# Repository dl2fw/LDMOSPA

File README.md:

# LDMOSPA
LDMOS PA based on the design of DJ0ABR - case from PCB Material<br>
Output power 750 or 1500 Watt - depends on if you use 1 or 2 double mosfets<br>
The PA can be either water or air cooled - the case makes both possible - I prefer the water cooled version<br>
The front has the same size as DB5AT's Wolf SDR case based on PCB Material<br>
All gerbers are available here<br>
I tried to gather all schematics and gerbers for the PA<br>
Also BOMS for Digikey, Reichelt and Aliexpress are in the BOM folder<br>
The water cooler is a ready available one (Digikey,...) for app. 65€<br>

Link to dj0abr's homepage with further information in german and english:

https://www.dj0abr.de/

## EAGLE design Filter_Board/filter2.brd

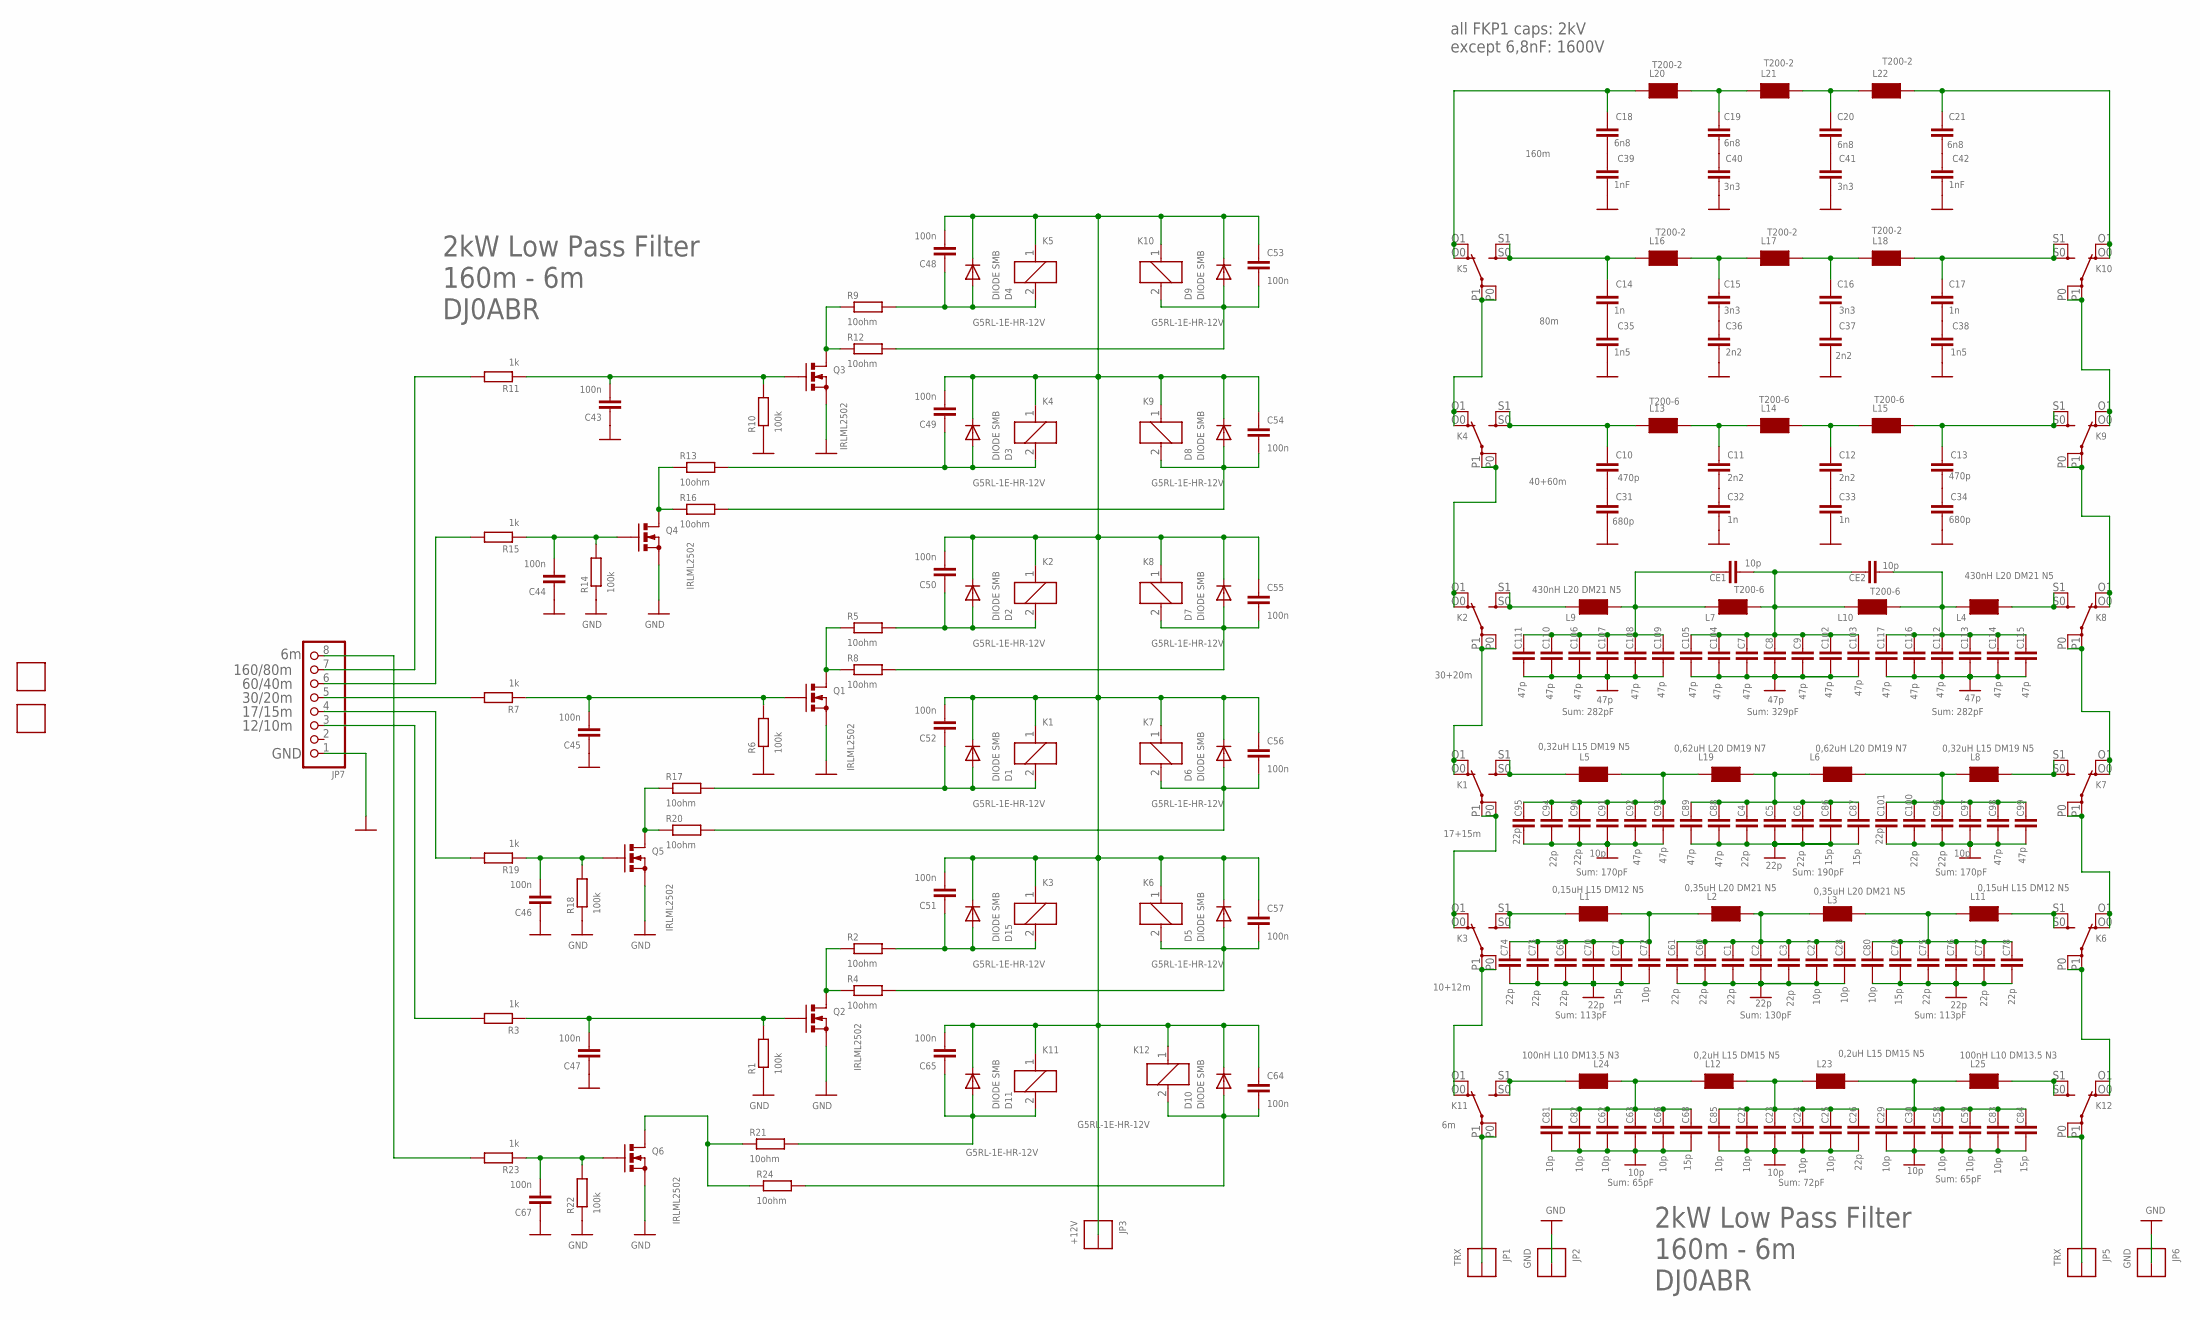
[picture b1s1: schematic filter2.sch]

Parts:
C1, C2, C3, C4, C5, C6, C26, C60, C61, C69, C70, C73, C74, C75, C76, C77, C78, C90, C94, C95, C96, C100, C101: 22p; C1812K
C7, C8, C9, C88, C89, C92, C93, C98, C99, C102, C103, C104, C105, C106, C107, C108, C109, C110, C111, C112, C113, C114, C115, C116, C117: 47p; C1812K
C10, C13: 470p; C150-064X183
C11, C12, C36, C37: 2n2; C225-074X268
C14, C17, C32, C33: 1n; C225-062X268
C15, C16: 3n3; C225-074X268
C18, C19, C20, C21: 6n8; C225-074X268
C22, C23, C24, C25, C27, C28, C29, C30, C58, C59, C62, C63, C66, C72, C80, C81, C82, C83, C85, C91, C97: 10p; C1812K
C31, C34: 680p; C150-064X183
C35, C38: 1n5; C225-074X268
C39, C42: 1nF; C225-074X268
C40, C41: 3n3; C225-087X268
C43, C44, C45, C46, C47, C48, C49, C50, C51, C52, C53, C54, C55, C56, C57, C64, C65, C67: 100n; C0603K
C68, C71, C79, C84, C86, C87: 15p; C1812K
CE1, CE2: 10p; C1812K
D1, D2, D3, D4, D5, D6, D7, D8, D9, D10, D11, D15: DIODE SMB; SMB
FID1, FID2: FIDUCIAL
JP1, JP5: TRX; THICKPIN
JP2, JP6: GND; THICKPIN
JP3: +12V; THICKPIN
JP7: PINHD-1X8; 1X08
K1, K2, K3, K4, K5, K6, K7, K8, K9, K10, K11, K12: G5RL-1E-HR-12V; G2RE
L1, L11: 0,15uH L15 DM12 N5; LUFTSPULE_L15XDM14
L2, L3: 0,35uH L20 DM21 N5; LUFTSPULE_L17XDM20
L4, L9: 430nH L20 DM21 N5; LUFTSPULE_20X20RM20
L5, L8: 0,32uH L15 DM19 N5; LUFTSPULR_L15XDM20
L6, L19: 0,62uH L20 DM19 N7; LUFTSPULE_20X20RM20
L7, L10, L13, L14, L15: T200-6; KERN200_STEHEND_2PIN
L12, L23: 0,2uH L15 DM15 N5; LUFTSPULE_L15XDM14
L16, L17, L18, L20, L21, L22: T200-2; KERN200_STEHEND_2PIN
L24, L25: 100nH L10 DM13.5 N3; LUFTSPULE_10X13K5
Q1, Q2, Q3, Q4, Q5, Q6: IRLML2502; SOT23
R1, R6, R10, R14, R18, R22: 100k; R0603
R2, R4, R5, R8, R9, R12, R13, R16, R17, R20, R21, R24: 10ohm; R0603
R3, R7, R11, R15, R19, R23: 1k; R0603

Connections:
+12V: C48.2, C49.2, C50.2, C51.2, C52.2, C53.1, C54.1, C55.1, C56.1, C57.1, C64.1, C65.2, D1.C, D2.C, D3.C, D4.C, D5.C, D6.C, D7.C, D8.C, D9.C, D10.C, D11.C, D15.C, JP3.1, K1.1, K2.1, K3.1, K4.1, K5.1, K6.1, K7.1, K8.1, K9.1, K10.1, K11.1, K12.1
GND: C1.2, C2.2, C3.2, C4.2, C5.2, C6.2, C7.2, C8.2, C9.2, C22.2, C23.2, C24.2, C25.2, C26.2, C27.2, C28.2, C29.2, C30.2, C31.2, C32.2, C33.2, C34.2, C35.2, C36.2, C37.2, C38.2, C39.2, C40.2, C41.2, C42.2, C43.1, C44.1, C45.1, C46.1, C47.1, C58.2, C59.2, C60.2, C61.2, C62.2, C63.2, C66.2, C67.1, C68.2, C69.2, C70.2, C71.2, C72.2, C73.2, C74.2, C75.2, C76.2, C77.2, C78.2, C79.2, C80.2, C81.2, C82.2, C83.2, C84.2, C85.2, C86.2, C87.2, C88.2, C89.2, C90.2, C91.2, C92.2, C93.2, C94.2, C95.2, C96.2, C97.2, C98.2, C99.2, C100.2, C101.2, C102.2, C103.2, C104.2, C105.2, C106.2, C107.2, C108.2, C109.2, C110.2, C111.2, C112.2, C113.2, C114.2, C115.2, C116.2, C117.2, JP2.1, JP6.1, JP7.1, Q1.2 (S), Q2.2 (S), Q3.2 (S), Q4.2 (S), Q5.2 (S), Q6.2 (S), R1.1, R6.1, R10.1, R14.1, R18.1, R22.1
unnamed: K6.P0, K6.P1, K12.O0 (O), K12.O1 (O)
unnamed: K3.S0 (S), K3.S1 (S), L1.P$1 (1)
unnamed: K1.P0, K1.P1, K3.O0 (O), K3.O1 (O)
unnamed: C75.1, C76.1, C77.1, C78.1, C79.1, C80.1, L3.P$2 (2), L11.P$1 (1)
unnamed: K1.S0 (S), K1.S1 (S), L5.P$1 (1)
unnamed: K1.O0 (O), K1.O1 (O), K2.P0, K2.P1
unnamed: C1.1, C2.1, C3.1, C27.1, C28.1, C60.1, C61.1, L2.P$2 (2), L3.P$1 (1)
unnamed: K2.S0 (S), K2.S1 (S), L9.P$1 (1)
unnamed: K2.O0 (O), K2.O1 (O), K4.P0, K4.P1
unnamed: K8.S0 (S), K8.S1 (S), L4.P$2 (2)
unnamed: K4.O0 (O), K4.O1 (O), K5.P0, K5.P1
unnamed: C106.1, C107.1, C108.1, C109.1, C110.1, C111.1, CE1.1, L7.1, L9.P$2 (2)
unnamed: K7.S0 (S), K7.S1 (S), L8.P$2 (2)
unnamed: Q2.3 (D), R2.1, R4.1
unnamed: K6.S0 (S), K6.S1 (S), L11.P$2 (2)
unnamed: K6.O0 (O), K6.O1 (O), K7.P0, K7.P1
unnamed: K7.O0 (O), K7.O1 (O), K8.P0, K8.P1
unnamed: K8.O0 (O), K8.O1 (O), K9.P0, K9.P1
unnamed: K9.O0 (O), K9.O1 (O), K10.P0, K10.P1
unnamed: C47.2, Q2.1 (G), R1.2, R3.1
unnamed: C90.1, C91.1, C92.1, C93.1, C94.1, C95.1, L5.P$2 (2), L19.P$1 (1)
unnamed: C4.1, C5.1, C6.1, C86.1, C87.1, C88.1, C89.1, L6.P$1 (1), L19.P$2 (2)
unnamed: C96.1, C97.1, C98.1, C99.1, C100.1, C101.1, L6.P$2 (2), L8.P$1 (1)
unnamed: C18.1, K5.O0 (O), K5.O1 (O), L20.1
unnamed: C7.1, C8.1, C9.1, C102.1, C103.1, C104.1, C105.1, CE1.2, CE2.1, L7.2, L10.1
unnamed: C112.1, C113.1, C114.1, C115.1, C116.1, C117.1, CE2.2, L4.P$1 (1), L10.2
unnamed: C10.1, K4.S0 (S), K4.S1 (S), L13.1
unnamed: C11.1, L13.2, L14.1
unnamed: C12.1, L14.2, L15.1
unnamed: C13.1, K9.S0 (S), K9.S1 (S), L15.2
unnamed: C14.1, K5.S0 (S), K5.S1 (S), L16.1
unnamed: C15.1, L16.2, L17.1
unnamed: C16.1, L17.2, L18.1
unnamed: C17.1, K10.S0 (S), K10.S1 (S), L18.2
unnamed: K3.P0, K3.P1, K11.O0 (O), K11.O1 (O)
unnamed: C19.1, L20.2, L21.1
unnamed: C20.1, L21.2, L22.1
unnamed: Q1.3 (D), R5.1, R8.1
unnamed: C45.2, Q1.1 (G), R6.2, R7.1
unnamed: Q3.3 (D), R9.1, R12.1
unnamed: C43.2, Q3.1 (G), R10.2, R11.1
unnamed: Q4.3 (D), R13.1, R16.1
unnamed: C44.2, Q4.1 (G), R14.2, R15.1
unnamed: Q5.3 (D), R17.1, R20.1
unnamed: C46.2, Q5.1 (G), R18.2, R19.1
unnamed: JP7.5, R7.2
unnamed: JP7.6, R15.2
unnamed: JP7.7, R11.2
unnamed: C22.1, C23.1, C24.1, C25.1, C26.1, C85.1, L12.P$2 (2), L23.P$1 (1)
unnamed: C21.1, K10.O0 (O), K10.O1 (O), L22.2
unnamed: C69.1, C70.1, C71.1, C72.1, C73.1, C74.1, L1.P$2 (2), L2.P$1 (1)
unnamed: C13.2, C34.1
unnamed: C21.2, C42.1
unnamed: C20.2, C41.1
unnamed: C19.2, C40.1
unnamed: C18.2, C39.1
unnamed: C10.2, C31.1
unnamed: C11.2, C32.1
unnamed: C12.2, C33.1
unnamed: C17.2, C38.1
unnamed: C16.2, C37.1
unnamed: C15.2, C36.1
unnamed: C14.2, C35.1
unnamed: JP7.4, R19.2
unnamed: JP7.3, R3.2
unnamed: JP1.1, K11.P0, K11.P1
unnamed: K11.S0 (S), K11.S1 (S), L24.P$1 (1)
unnamed: Q6.3 (D), R21.1, R24.1
unnamed: C62.1, C63.1, C66.1, C68.1, C81.1, C82.1, L12.P$1 (1), L24.P$2 (2)
unnamed: C29.1, C30.1, C58.1, C59.1, C83.1, C84.1, L23.P$2 (2), L25.P$1 (1)
unnamed: K12.S0 (S), K12.S1 (S), L25.P$2 (2)
unnamed: JP5.1, K12.P0, K12.P1
unnamed: C67.2, Q6.1 (G), R22.2, R23.1
unnamed: JP7.8, R23.2
R1: C50.1, D2.A, K2.2, R5.2
R2: C51.1, D15.A, K3.2, R2.2
R3: C52.1, D1.A, K1.2, R17.2
R4: C65.1, D11.A, K11.2, R21.2
R5: C49.1, D3.A, K4.2, R13.2
R8: C48.1, D4.A, K5.2, R9.2
RB6: C64.2, D10.A, K12.2, R24.2
RB10: C57.2, D5.A, K6.2, R4.2
RB15: C56.2, D6.A, K7.2, R20.2
RB20: C55.2, D7.A, K8.2, R8.2
RB40: C54.2, D8.A, K9.2, R16.2
RB80: C53.2, D9.A, K10.2, R12.2

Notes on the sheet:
10+12m
30+20m
40+60m
80m
160m
17+15m
160/80m
60/40m
30/20m
17/15m
12/10m
GND
2kW Low Pass Filter 160m - 6m DJ0ABR
all FKP1 caps: 2kV except 6,8nF: 1600V
Sum: 282pF
Sum: 329pF
Sum: 170pF
Sum: 190pF
Sum: 113pF
Sum: 130pF
Sum: 65pF
Sum: 72pF

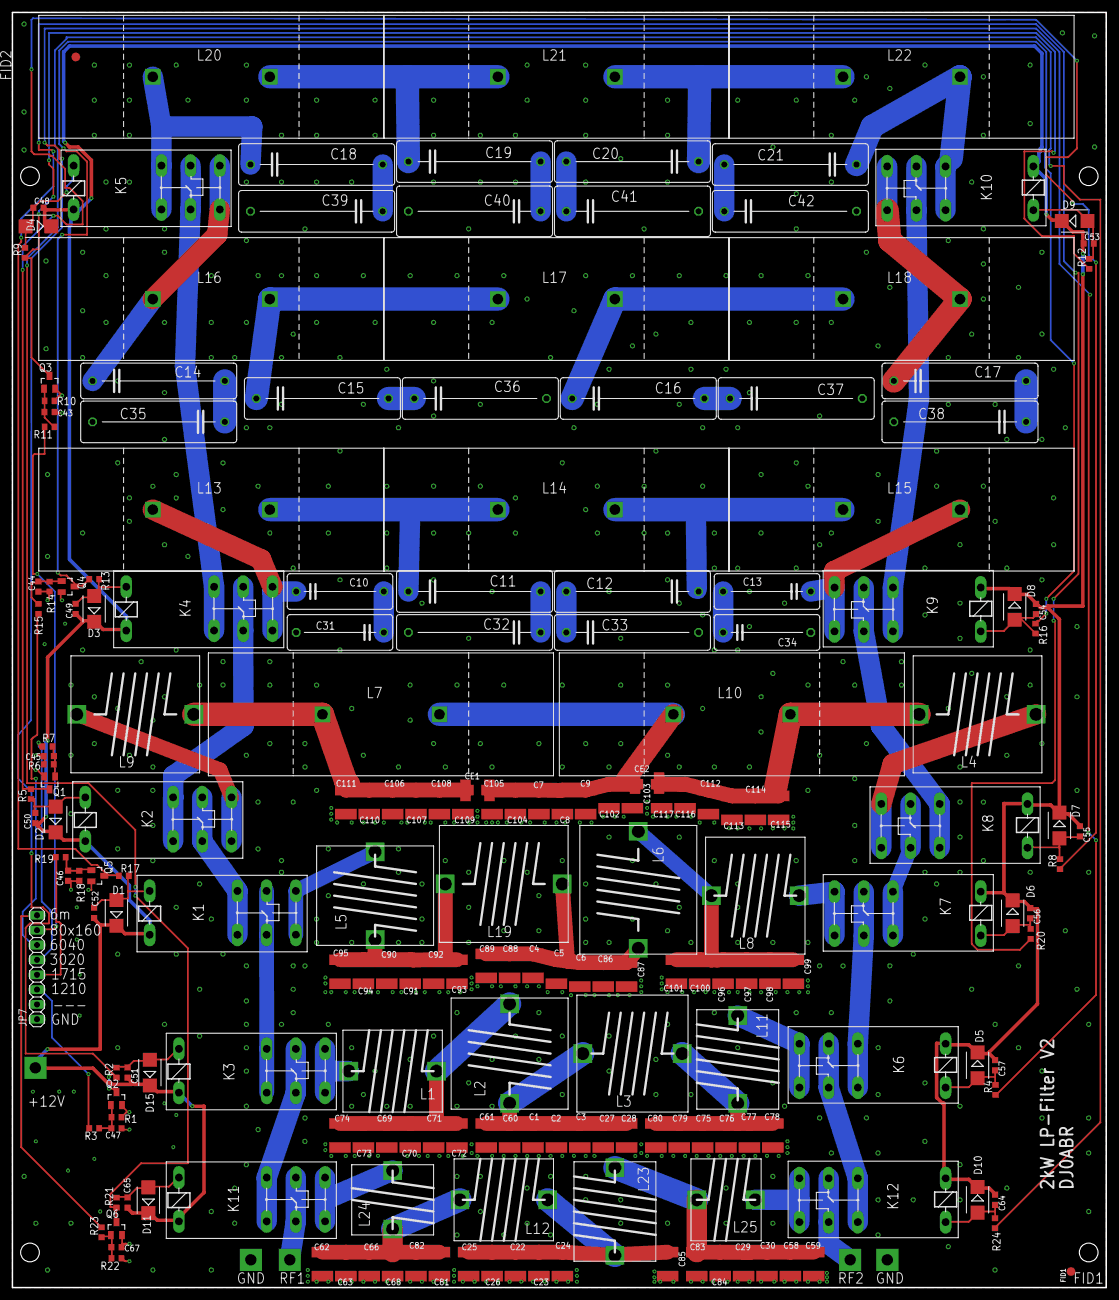
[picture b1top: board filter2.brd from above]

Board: 2 copper layers, 187.0 x 218.0 mm, 206 parts (0 on the bottom side), 88 nets.

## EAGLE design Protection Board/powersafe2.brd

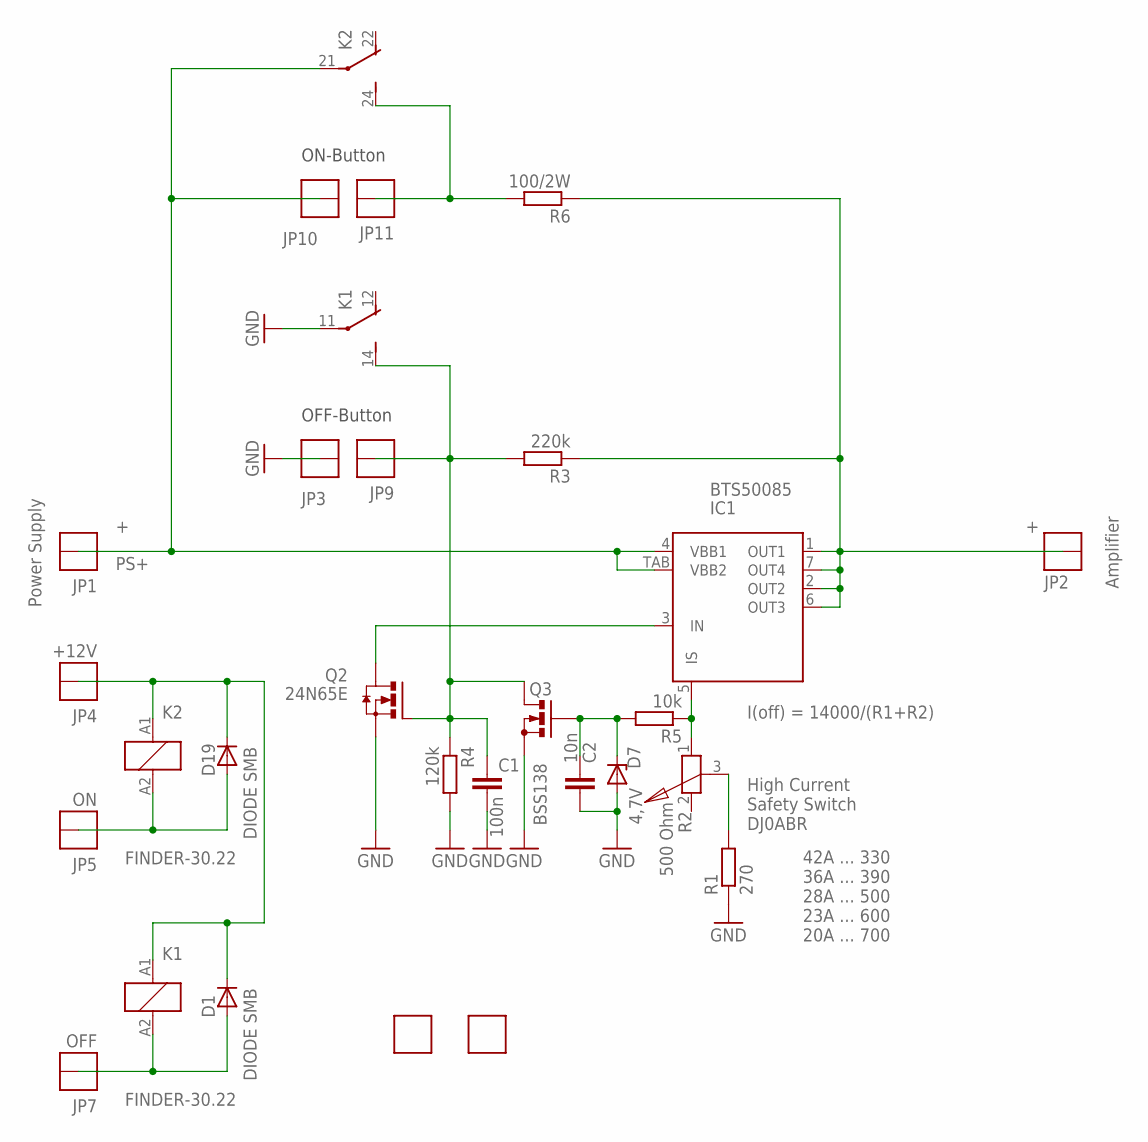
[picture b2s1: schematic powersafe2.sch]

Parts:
C1: 100n; C0603K
C2: 10n; C0603K
D1, D19: DIODE SMB; SMB
D7: 4,7V; SMA
FID1, FID2: FIDUCIAL
IC1: BTS50085; PG-TO220-7-4
JP1, JP2: THICKPINPIN_4QMM; PIN_4QMM
JP3, JP9, JP10, JP11: THICKPINSQUARE; THICKPIN
JP4: +12V; THICKPIN_OCT
JP5: ON; THICKPIN_OCT
JP7: OFF; THICKPIN_OCT
K1, K2: FINDER-30.22
Q2: 24N65E; D2PACK
Q3: BSS138; SOT23
R1: 270; R0603
R2: 500 Ohm; MINIPOTI
R3: 220k; R0603
R4: 120k; R0603
R5: 10k; R0603
R6: 100/2W; P0613/15

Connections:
GND: C1.2, C2.2, D7.A, JP3.1, K1.11, Q2.3 (S), Q3.2 (S), R1.1, R4.2
unnamed: C2.1, D7.C, Q3.1 (G), R5.2
unnamed: IC1.3 (IN), Q2.2 (D)
unnamed: C1.1, JP9.1, K1.14 (S), Q2.1 (G), Q3.3 (D), R3.2, R4.1
unnamed: IC1.5 (IS), R2.1, R5.1
unnamed: JP11.1, K2.24 (S), R6.2
unnamed: D19.A, JP5.1, K2.A2 (2)
unnamed: D1.C, D19.C, JP4.1, K1.A1 (1), K2.A1 (1)
unnamed: R1.2, R2.3
unnamed: D1.A, JP7.1, K1.A2 (2)
PA+: IC1.1 (OUT1), IC1.2 (OUT2), IC1.6 (OUT3), IC1.7 (OUT4), JP2.P$1, R3.1, R6.1
PS+: IC1.4 (VBB1), IC1.TAB (VBB2), JP1.P$1, JP10.1, K2.21

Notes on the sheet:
I(off) = 14000/(R1+R2)
High Current Safety Switch DJ0ABR
42A ... 330 36A ... 390 28A ... 500 23A ... 600 20A ... 700
OFF-Button
ON-Button
Amplifier
Power Supply

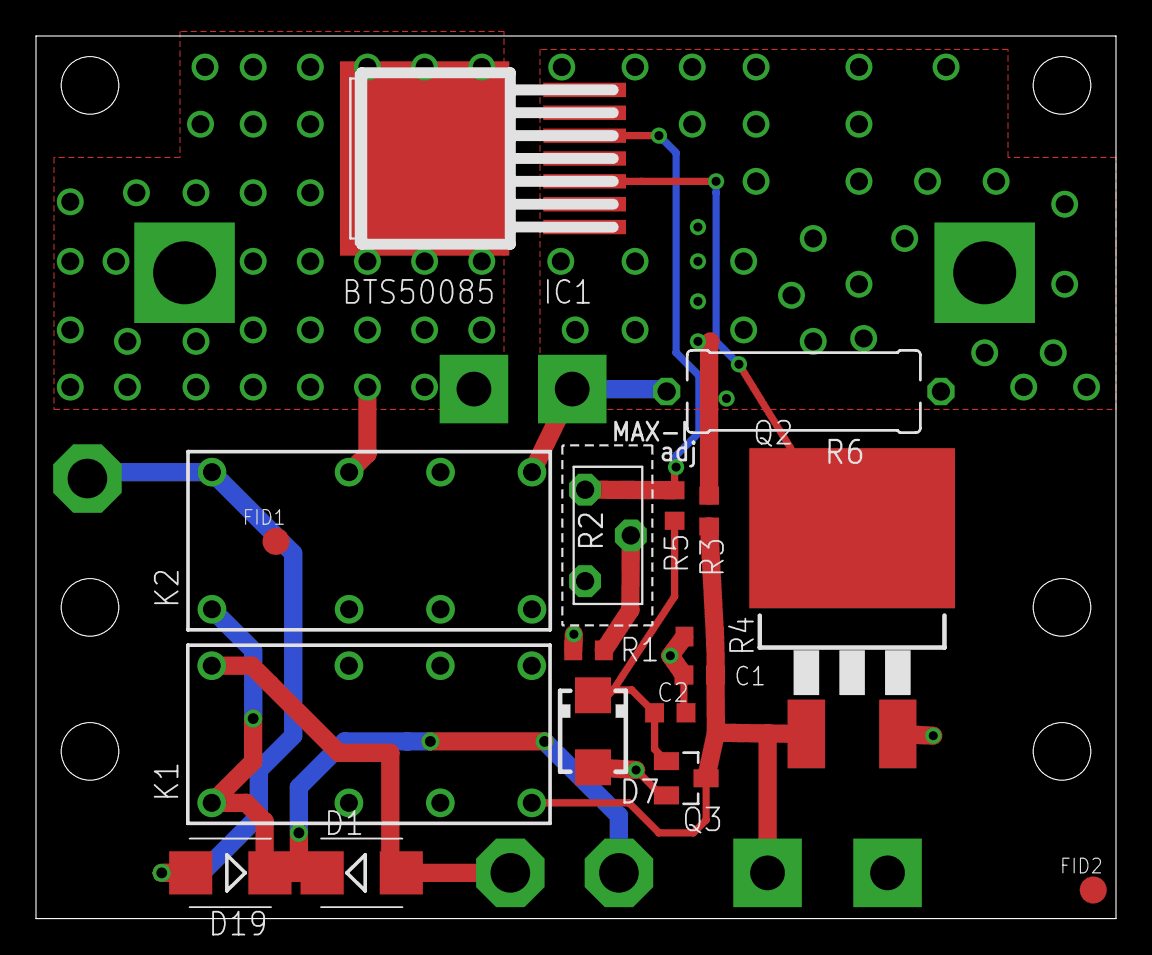
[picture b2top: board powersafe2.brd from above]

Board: 2 copper layers, 60.0 x 49.0 mm, 27 parts (0 on the bottom side), 12 nets.

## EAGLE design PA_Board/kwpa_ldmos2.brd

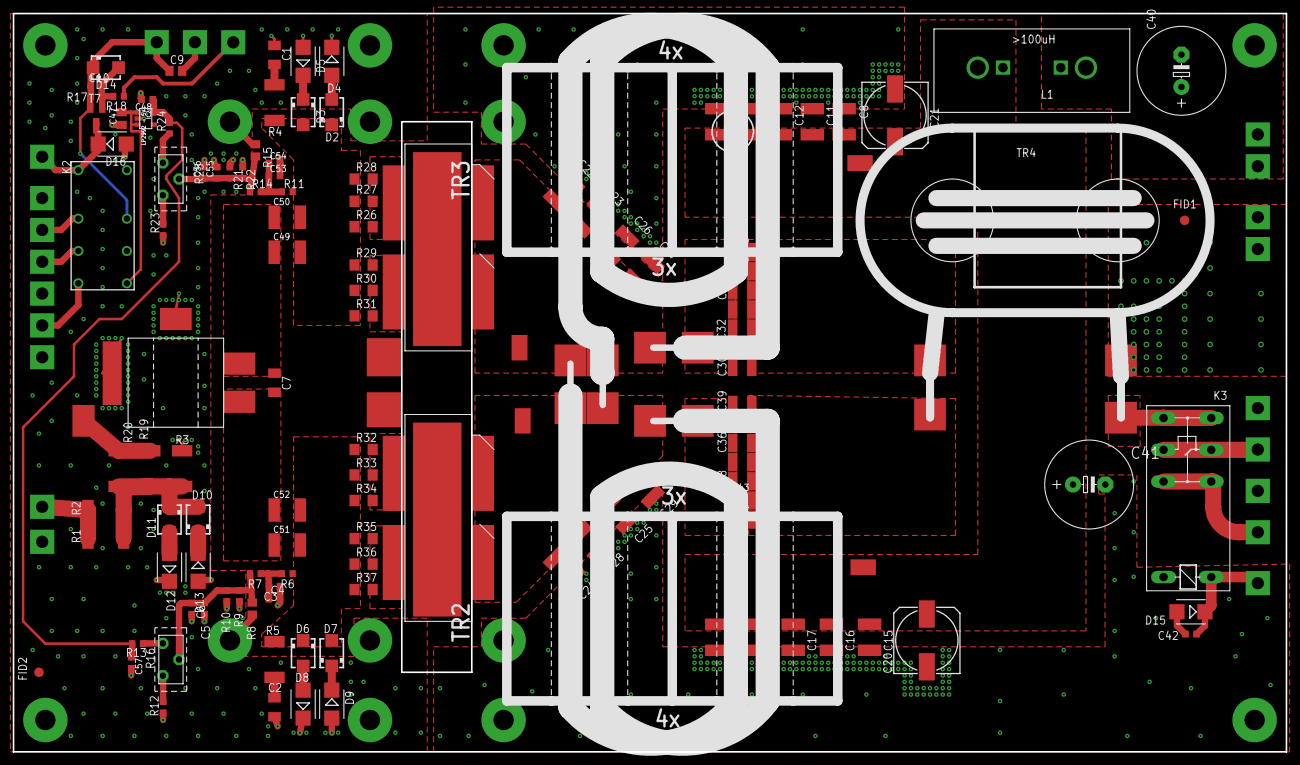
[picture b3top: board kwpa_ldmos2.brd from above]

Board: 2 copper layers, 200.0 x 116.0 mm, 161 parts (0 on the bottom side), 49 nets.

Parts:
C1, C2: 10n/450V; C1206K
C3, C5, C53, C55, C57: 1u; C0603K
C4, C42, C54: 100n; C0603K
C6, C10, C56: 10n; C0603K
C7: opt.; C1206K
C8, C11, C15, C16: 10n; C1812K
C9: 10u/25; C0805K
C12, C13, C17, C18, C49, C50, C51, C52: 100n; C1812K
C14, C19: 1u; C1812K
C20, C21: 100u/63; 153CLV-1014
C22, C23, C24, C25, C26, C27, C28, C29: 120p; C1812K
C30, C31, C32, C33, C34, C35, C36, C37, C38, C39, C43, C44, C45, C46: 10n; C1210K
C40, C41: 470uF/63V; E5-13
C47: 10u; C0805K
C48: 10u; C0603K
D2, D6: 8,2V; SMA
D3, D7: 4,7V; SMA
D4, D5, D8, D9, D12, D13, D15, D16: DIODE SMB; SMB
D10, D11: SMBJ15A; SMA
D14: 6,2V/1W; SMA
FID1, FID2: FIDUCIAL
H1, H2, H3, H4, H5, H6, H7, H8, H9, H10, H11, H12, H13, H14: HOLE_32; HOLE32
IC2: LP2992 - 5V; SOT23-5
JP1: RF_IN; THICKPIN
JP2, JP3, JP8, JP10, JP12, JP14, JP15, JP20, JP22: GND; THICKPIN
JP4: RXBYP-2; THICKPIN
JP5: +12..+14V; THICKPIN
JP7: RX_BYP1; THICKPIN
JP9: PTT; THICKPIN
JP11: RF-OUT; THICKPIN
JP13, JP16: +50V; THICKPIN
JP17, JP18: RELAIS; THICKPIN
JP19: TO_ATT; THICKPIN
JP21: FROM_ATT; THICKPIN
K2: FINDER-30.22
K3: G5RL-1E-HR-12V; G2RE
L1: >100uH; KERN90_STEHEND_2PIN
R1, R2, R19, R20: 22/2W; R2512
R3: 100/2W; R2512
R4, R5: 10/2W; R2512
R6, R11: 1k; R0603
R7, R14: 470; R0603
R8, R15: NTC0805J5K0; R0805
R9, R21: 560; R0603
R10, R22: 5k6; R0603
R12, R23: 47; R0603
R13, R24: 270; R0603
R16, R25: 250; MINIPOTI
R17, R18: 10k; R0603
R26, R27, R28, R29, R30, R31, R32, R33, R34, R35, R36, R37: 10; R1206
T1, T2: BLF188
T1P3, T1P4, T1S3, T1S4: SMDPAD2,5X4
T7: IRLML6401; SOT23
TR1: 4:1 Laird 28B0562-100; KW-INPUT_LAIRD_28B0562-100
TR2: DOPPELRINGKERN
TR3: DOPPELRINGKERN_REV
TR4: DOPPELLMANTEL_STEHEND

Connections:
ATTM: D10.A, D11.C, R1.2, R2.2, R3.2, R19.1, R20.1
BYP1: JP7.1, K2.12
DD1: C49.2, C50.2, D2.C, D3.A, R4.1, R11.2, R26.1, R27.1, R28.1, R29.1, R30.1, R31.1
DD2: C51.2, C52.2, D6.C, D7.A, R5.2, R6.2, R32.1, R33.1, R34.1, R35.1, R36.1, R37.1
DI1: C7.1, C49.1, C50.1, TR1.OUT2
DI2: C7.2, C51.1, C52.1, TR1.OUT1
DRAIN1: C22.2, C23.2, C26.2, C27.2, T1P4.P$1, T2.1, T2.2, TR2.P1, TR3.P2, TR3.S1
DRAIN2: C24.2, C25.2, C28.2, C29.2, T1.1, T1.2, T1S3.P$1, TR2.P2, TR2.S1, TR3.P1
G1: R26.2, R27.2, R28.2, T2.3
G2: R29.2, R30.2, R31.2, T2.4
G3: R32.2, R33.2, R34.2, T1.3
G4: R35.2, R36.2, R37.2, T1.4
GND: C1.1, C2.2, C3.2, C4.2, C5.2, C6.2, C8.2, C9.2, C11.2, C12.2, C13.2, C14.2, C15.1, C16.1, C17.1, C18.1, C19.1, C20.-, C21.-, C22.1, C23.1, C24.1, C25.1, C26.1, C27.1, C28.1, C29.1, C40.-, C41.-, C42.1, C47.1, C48.2, C53.2, C54.2, C55.2, C56.2, C57.2, D4.C, D5.A, D8.C, D9.A, D12.C, D13.A, D15.A, D16.A, H1.P$1, H2.P$1, H3.P$1, H4.P$1, H5.P$1, H6.P$1, H7.P$1, H8.P$1, H9.P$1, H10.P$1, H11.P$1, H12.P$1, H13.P$1, H14.P$1, IC2.2, JP2.1, JP3.1, JP8.1, JP10.1, JP12.1, JP14.1, JP15.1, JP20.1, JP22.1, K2.A2, K3.2, R3.1, R8.1, R9.1, R10.1, R12.1, R15.1, R21.1, R22.1, R23.1, TR1.COM, TR1.GND, TR4.S1
unnamed: JP21.1, R1.1, R2.1
unnamed: C47.2, IC2.1, IC2.3, K2.24
unnamed: D10.C, D13.C
unnamed: JP11.1, K3.P0, K3.P1
unnamed: C1.2, R4.2
unnamed: C2.1, R5.1
unnamed: JP19.1, K2.14
unnamed: C3.1, C4.1, R6.1, R7.2
unnamed: C5.1, C6.1, R7.1, R8.2, R9.2, R10.2, R16.3
unnamed: R12.2, R16.2
unnamed: R13.1, R16.1
unnamed: C48.1, C57.1, IC2.5, R13.2, R24.2
unnamed: D3.C, D5.C
unnamed: D2.A, D4.A
unnamed: C53.1, C54.1, R11.1, R14.2
unnamed: D7.C, D9.C
unnamed: D6.A, D8.A
unnamed: D11.A, D12.A
unnamed: C55.1, C56.1, R14.1, R15.2, R21.2, R22.2, R25.3
unnamed: R23.2, R25.2
unnamed: R24.1, R25.1
unnamed: C10.2, D14.A, R17.2, R18.2, T7.1
unnamed: JP4.1, K3.O0, K3.O1
unnamed: JP9.1, R18.1
unnamed: R19.2, R20.2, TR1.IN
OUTP1: C30.1, C31.1, C32.1, C33.1, C34.1, C45.1, C46.1, TR3.S2
OUTP2: C35.1, C36.1, C37.1, C38.1, C39.1, C43.1, C44.1, TR2.S2
OUTR1: K3.S0, K3.S1, TR4.P1
OUTS1: C30.2, C31.2, C32.2, C33.2, C34.2, C45.2, C46.2, TR4.S2
OUTS2: C35.2, C36.2, C37.2, C38.2, C39.2, C43.2, C44.2, TR4.P2
RELAIS: C42.2, D15.C, JP18.1, K3.1
RELAISOUT: D16.C, JP17.1, K2.A1, T7.3
RFIN: JP1.1, K2.11
U12: C9.1, C10.1, D14.C, JP5.1, K2.21, R17.1, T7.2
UIN: C40.+, JP13.1, JP16.1, L1.P$1
UVERS: C8.1, C11.1, C12.1, C13.1, C14.1, C15.2, C16.2, C17.2, C18.2, C19.2, C20.+, C21.+, C41.+, L1.P$2, T1P3.P$1, T1S4.P$1

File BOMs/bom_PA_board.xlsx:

|  |  |  |  | Reichelt | Digikey | Preis | Summe
Qty | Device | Type | Package | Parts
2 | 250 ohms | Trimm Poti | RM 5 / 2,5mm | R16, R25 | 64Y-200 |  | 1.6 | 3.2
2 | 470uF/63V | electrolytic cap. | 12.5 (Dia.) x 20mm | C40, C41 | EB-A 470U 63 |  | 0.99 | 1.98
1 | Lesitungsrelais 12V G5RL-1E-HR-12V |  | G2RE | K3 | G5RL-1E-HR 12DC |  | 1.99 | 1.99
1 | IRLML6401 | P-CHANNEL MOS FET | SOT23 | T7 | IRLML 6401 |  | 0.82 | 0.82
1 | 10u | ceramic multilayer capacitor X7R | SMD 0603 | C48 | KEM X5R0603 10U |  | 0.13 | 0.13
3 | 10n | ceramic multilayer capacitor X7R | SMD 0603 | C6, C10, C56 | KEM X7R0603 10N |  | 0.03 | 0.09
2 | 1k | resistor | SMD 0603 | R6, R11 | SMD-0603 1,0K |  | 0.04 | 0.08
2 | 10k | resistor | SMD 0603 | R17, R18 | SMD-0603 10K |  | 0.04 | 0.08
2 | 270 | resistor | SMD 0603 | R13, R24 | SMD-0603 270 |  | 0.04 | 0.08
2 | 47 | resistor | SMD 0603 | R12, R23 | SMD-0603 47 |  | 0.04 | 0.08
2 | 470 | resistor | SMD 0603 | R7, R14 | SMD-0603 470 |  | 0.04 | 0.08
2 | 5k6 | resistor | SMD 0603 | R10, R22 | SMD-0603 5,6K |  | 0.04 | 0.08
2 | 560 | resistor | SMD 0603 | R9, R21 | SMD-0603 560 |  | 0.04 | 0.08
2 | 100u/63 | electrolytic cap. | Dia 11 max. | C20, C21 | TG-V 100U 63 |  | 1.1000000000000001 | 2.2000000000000002
3 | 100n | ceramic multilayer capacitor X7R | SMD 0603 | C4, C42, C54 | WAL 0603B104K500 |  | 0.02 | 0.06
5 | 1u | ceramic multilayer capacitor X7R | SMD 0603 | C3, C5, C53, C55, C57 | X5R-G0603 1,0/25 |  | 0.13 | 0.65
2 | 10u | ceramic multilayer capacitor X7R | SMD 0805 | C9, C47 | X5R-G0805 10/16 |  | 0.05 | 0.1
2 | 10n/500V | caramic capacitor 450V | SMD 1206 | C1, C2 |  | 311-1510-1-ND | 0.25 | 0.5
14 | 10n/500V | ceramic multilayer capacitor X7R | SMD 1210 | C30, C31, C32, C33, C34, C35, C36,C37, C38, C39, C43, C44, C45, C46 |  | 478-KGM32ER72H103KUCT-ND | 0.63 | 8.82
8 | 100n/600V | ceramic multilayer capacitor X7R | SMD 1812 | C12, C13, C17, C18, C49, C50, C51, C52 |  | 478-KGM43FR72J104KVCT-ND | 0.64 | 5.12
4 | 10n/1kV | ceramic multilayer capacitor X7R | SMD 1812 | C8, C11, C15, C16 |  | 1812AC103KAT1A | 0.49 | 1.96
8 | 120p/3kV | ceramic multilayer capacitor C0G | SMD 1812 | C22, C23, C24, C25, C26, C27, C28, C29 |  | CGA8L1C0G3F121K160KA | 0.75 | 6
2 | 1u/250V | ceramic multilayer capacitor X7R | SMD 1812 | C14, C19 |  | C1812X105K251T | 1 | 2
8 | DIODE SMB | standard Schottky Diode | SMB | D4, D5, D8, D9, D12, D13, D15, D16 |  | S2MFSCT-ND | 0.41 | 3.28
2 | NTC0805J5K0 | NTC | SMD 0805 | R8, R15 |  | 1712-NTC0805J5K0CT-ND | 1.2 | 2.4
12 | 10 | resistor | SMD 1206 | R26, R27, R28, R29, R30, R31, R32,R33, R34, R35, R36, R37 |  | 541-10.0UCT-ND | 0.37 | 4.4399999999999995
2 | 10/2W | resistor | SMD 2512 | R4, R5 |  | A121124CT-ND | 0.62 | 1.24
1 | 100/2W | resistor | SMD 2512 | R3 |  | CRM2512-FX-1000ELFCT-N | 0.5 | 0.5
4 | 22/2W | resistor | SMD 2512 | R1, R2, R19, R20 |  | CRM2512-JW-220ELF | 0.56999999999999995 | 2.2799999999999998
1 | LP2992 - 5V | 5V voltage regulator | SOT23-5 | IC2 |  | LP2992AIM5X-5.0/NOPBCT-ND | 1.5 | 1.5
2 | 4,7V | zener diode | SMA | D3, D7 |  | KDZVTFTR4.7BCT-ND | 0.44 | 0.88
1 | 6,2V/1W | zener diode | SMA | D14 |  | KDZVTFTR6.2BCT-ND | 0.44 | 0.44
2 | 8,2V | zener diode | SMA | D2, D6 |  | SMAJ4738A-TPCT-ND | 0.38 | 0.76
2 | SMBJ15A | TVS protection diode | SMA | D10, D11 |  | SMBJ15ALFCT-ND | 0.37 | 0.74
1 | BLF188 | BLF188XR (or two BLF188XR) | BLF188 | T1, T2 |  | xxx |  | 0
1 | 12V Relais | Relais 12V Kontakt: DPDT |  | K2 |  | PB1632-ND | 3.85 | 3.85
8 | Ferrite Core |  | Laird 28B1020-100 |  |  | 240-2081-ND | 2.4700000000000002 | 19.760000000000002
1 | Ferrite Core | Input Transformer | Laird 28B0562-100 | TR1 |  | 240-2607-ND | 0.54 | 0.54
1 | Ferrite Ring | Ub EMI suppression | any code possible Dia abt. 30mm | L1 |  | 732-1536-ND | 5.84 | 5.84
 | Water Cooler |  |  |  |  | CP4A-114B-108E-ND |  | 80.430000000000007
 | Copper Plate |  | 10mmm thick
 | Power Mosfet | BLF188 or MRFX1K80 | app. 150€
 | Board |  | Size: 116*200mm | select high copper coating! |  | from JLCPCB | 5 Pieces | 30.9
 |  |  |  |  |  |  | Sum | 188.79000000000002 | €
